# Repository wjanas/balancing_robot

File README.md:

# balancing_robot
Balancing robot project

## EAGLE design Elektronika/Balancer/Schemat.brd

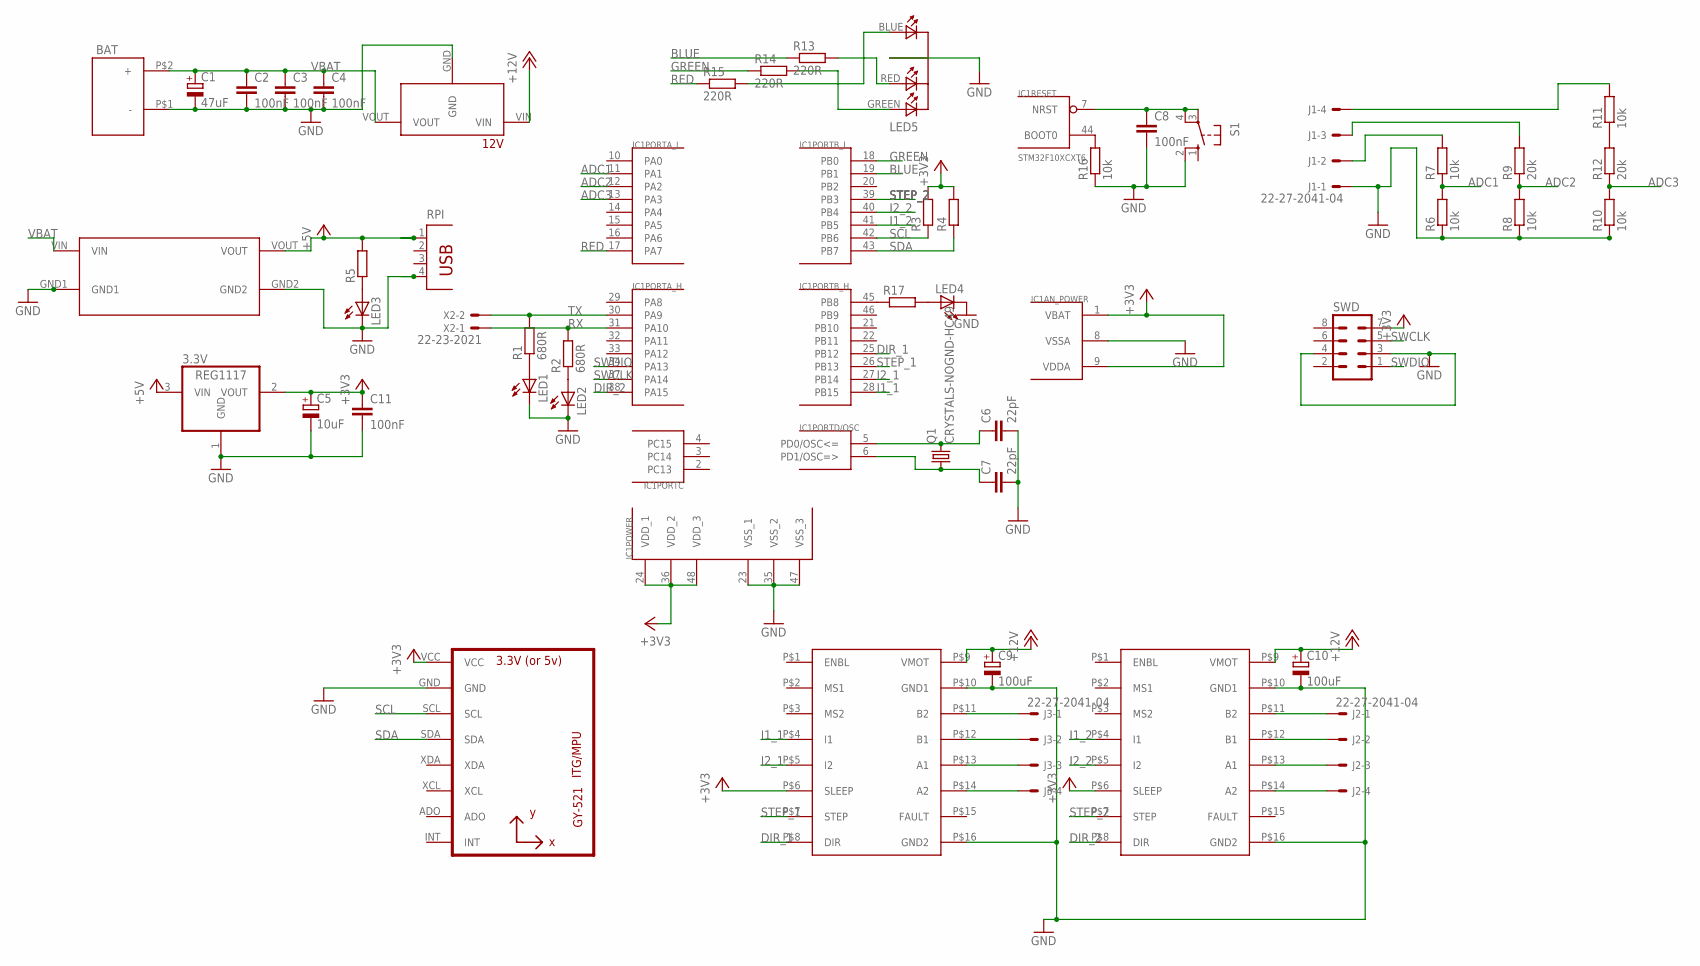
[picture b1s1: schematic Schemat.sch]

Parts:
3.3V: REG1117; SOT223
12V: 12V_VOLTAGE_REGULATOR; 9V_VOLTAGE_REGULATOR
BAT: DEANS; DEAN
C1: 47uF; E2-5
C2, C3, C4: 100nF; C0603K
C5: 10uF; E2-5
C6, C7: 22pF; C0603K
C8: 100nF; C050-030X075
C9, C10: 100uF; E2,5-7
C11: 100nF; C0603
DRV1, DRV2: POLOLU-MP6500; STEPPER-CARRIER
IC1: STM32F10XCXT6; TQFP48
J1, J2, J3: 22-27-2041-04; 6410-04
LED1, LED2: LEDSML0603; SML0603
LED3, LED4: LED5MM
LED5: LED-DIP-3; DIP-4
Q1: CRYSTALS-NOGND-HC49; HC49
R1, R2: 680R; R0805
R3, R4, R5, R17: R-EU_R0805; R0805
R6, R7, R8, R10, R11, R16: 10k; R0805
R9, R12: 20k; R0805
R13, R14, R15: 220R; R0805
RPI: PN87520
S1: 10-XX; B3F-10XX
SWD: MA04-2
U1: GY-521MPU6050; GY-521
U$1: DC-DC
X2: 22-23-2021

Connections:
+3V3: 3.3V.2 (VOUT), C5.+, C11.1, DRV1.P$6 (SLEEP), DRV2.P$6 (SLEEP), IC1.1 (VBAT), IC1.9 (VDDA), IC1.24 (VDD_1), IC1.36 (VDD_2), IC1.48 (VDD_3), R3.2, R4.2, SWD.7, U1.VCC
+5V: 3.3V.3 (VIN), R5.2, RPI.1, U$1.VOUT
+12V: 12V.VIN, C9.+, C10.+, DRV1.P$9 (VMOT), DRV2.P$9 (VMOT)
ADC1: IC1.11 (PA1), R6.2, R7.1
ADC2: IC1.12 (PA2), R8.2, R9.1
ADC3: IC1.13 (PA3), R10.2, R12.1
BLUE: IC1.19 (PB1), R13.1
DIR_1: DRV1.P$8 (DIR), IC1.25 (PB12)
DIR_2: DRV2.P$8 (DIR), IC1.38 (PA15)
GND: 3.3V.1 (GND), 12V.GND, BAT.P$1 (-), C1.-, C2.2, C3.2, C4.2, C5.-, C6.2, C7.2, C8.2, C9.-, C10.-, C11.2, DRV1.P$10 (GND1), DRV1.P$16 (GND2), DRV2.P$10 (GND1), DRV2.P$16 (GND2), IC1.8 (VSSA), IC1.23 (VSS_1), IC1.35 (VSS_2), IC1.47 (VSS_3), J1.1, LED1.C, LED2.C, LED3.K (C), LED4.K (C), LED5.COMMON_CATHODE (COM-CATHODE), R6.1, R8.1, R10.1, R16.1, RPI.4, S1.2 (S1), SWD.3, SWD.4, U1.GND, U$1.GND1, U$1.GND2
GREEN: IC1.18 (PB0), R14.1
I1_1: DRV1.P$4 (I1), IC1.28 (PB15)
I1_2: DRV2.P$4 (I1), IC1.41 (PB5)
I2_1: DRV1.P$5 (I2), IC1.27 (PB14)
I2_2: DRV2.P$5 (I2), IC1.40 (PB4)
unnamed: LED1.A, R1.1
unnamed: LED2.A, R2.1
unnamed: IC1.44 (BOOT0), R16.2
unnamed: C7.1, IC1.6 (PD1/OSC=>), Q1.1
unnamed: LED5.GREEN, R14.2
unnamed: J1.2, R7.2
unnamed: LED3.A, R5.1
unnamed: J1.3, R9.2
unnamed: R11.1, R12.2
unnamed: J1.4, R11.2
unnamed: C8.1, IC1.7 (NRST), S1.3, S1.4 (P1)
unnamed: IC1.45 (PB8), R17.1
unnamed: LED4.A, R17.2
unnamed: LED5.RED, R13.2
unnamed: DRV2.P$11 (B2), J2.1
unnamed: LED5.BLUE, R15.2
unnamed: DRV1.P$12 (B1), J3.2
unnamed: DRV2.P$12 (B1), J2.2
unnamed: DRV2.P$13 (A1), J2.3
unnamed: DRV2.P$14 (A2), J2.4
unnamed: DRV1.P$11 (B2), J3.1
unnamed: DRV1.P$13 (A1), J3.3
unnamed: DRV1.P$14 (A2), J3.4
unnamed: C6.1, IC1.5 (PD0/OSC<=), Q1.2
RED: IC1.17 (PA7), R15.1
RX: IC1.31 (PA10), R2.2, X2.1
SCL: IC1.42 (PB6), R3.1, U1.SCL
SDA: IC1.43 (PB7), R4.1, U1.SDA
STEP_1: DRV1.P$7 (STEP), IC1.26 (PB13)
STEP_2: DRV2.P$7 (STEP), IC1.39 (PB3)
SWCLK: IC1.37 (PA14), SWD.5
SWDIO: IC1.34 (PA13), SWD.1
TX: IC1.30 (PA9), R1.2, X2.2
VBAT: 12V.VOUT, BAT.P$2 (+), C1.+, C2.1, C3.1, C4.1, U$1.VIN

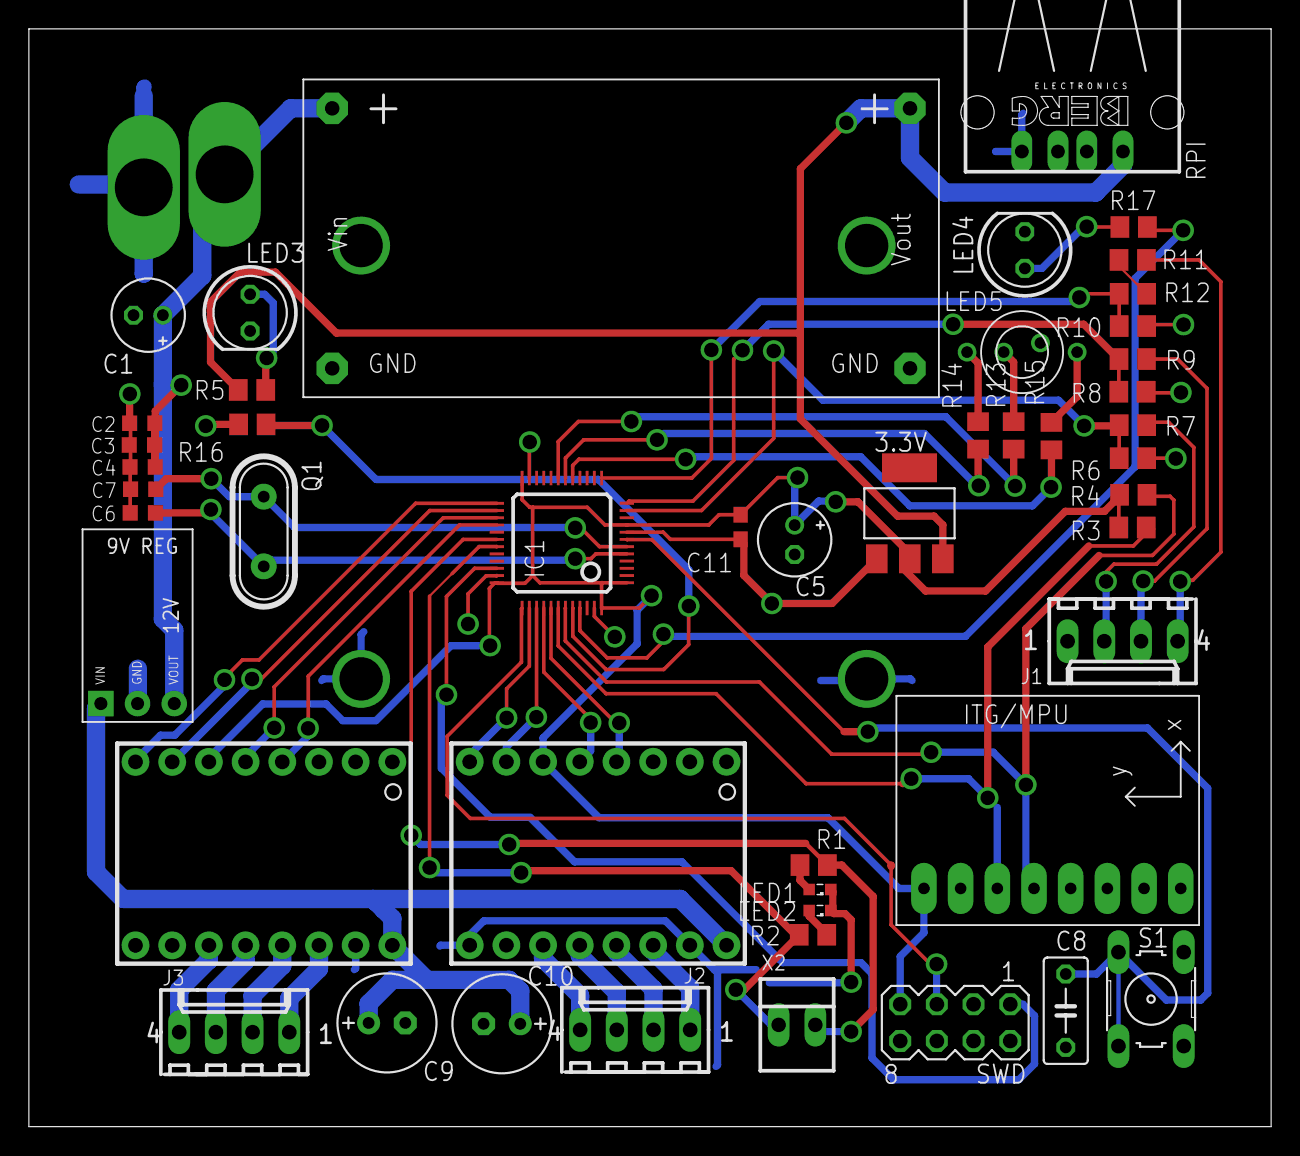
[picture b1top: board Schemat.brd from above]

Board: 2 copper layers, 86.0 x 76.0 mm, 49 parts (0 on the bottom side), 49 nets.

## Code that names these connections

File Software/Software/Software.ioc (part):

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Mcu.Name=STM32F100C(8-B)Tx
Mcu.Package=LQFP48
Mcu.UserName=STM32F100C8Tx
PA1.Signal=GPIO_Output
PA10.Mode=Asynchronous
PA10.Signal=USART1_RX
PA13.Mode=Serial_Wire
PA13.Signal=SYS_JTMS-SWDIO
PA14.Mode=Serial_Wire
PA14.Signal=SYS_JTCK-SWCLK
PA15.Signal=GPIO_Output
PA2.Signal=GPIO_Output
PA3.Signal=GPIO_Output
PA7.Signal=S_TIM3_CH2
PA9.Mode=Asynchronous
PA9.Signal=USART1_TX
PB0.Signal=S_TIM3_CH3
PB1.Signal=S_TIM3_CH4
PB12.Signal=GPIO_Output
PB13.Signal=GPIO_Output
PB14.Signal=GPIO_Output
PB15.Signal=GPIO_Output
PB3.Signal=GPIO_Output
PB4.Signal=GPIO_Output
PB5.Signal=GPIO_Output
PB6.Mode=I2C
PB6.Signal=I2C1_SCL
PB7.Mode=I2C
PB7.Signal=I2C1_SDA
PB8.Signal=GPIO_Output
PD0-OSC_IN.Mode=HSE-External-Oscillator
PD0-OSC_IN.Signal=RCC_OSC_IN
PD1-OSC_OUT.Mode=HSE-External-Oscillator
PD1-OSC_OUT.Signal=RCC_OSC_OUT
RCC.HSEDivPLL=RCC_HSE_PREDIV_DIV10
RCC.HSE_VALUE=16000000
RCC.SYSCLKFreq_VALUE=24000000
RCC.SYSCLKSource=RCC_SYSCLKSOURCE_PLLCLK
board=custom

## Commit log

2019-11-09 added RGB handling + converted to CubeIDE
2019-11-10 Added ADC and overdischarge protection
2019-11-10 Added routine for battery check
2020-05-09 cleanup
